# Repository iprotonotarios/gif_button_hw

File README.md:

# gif_button_hw
KiCad design files for gif_button

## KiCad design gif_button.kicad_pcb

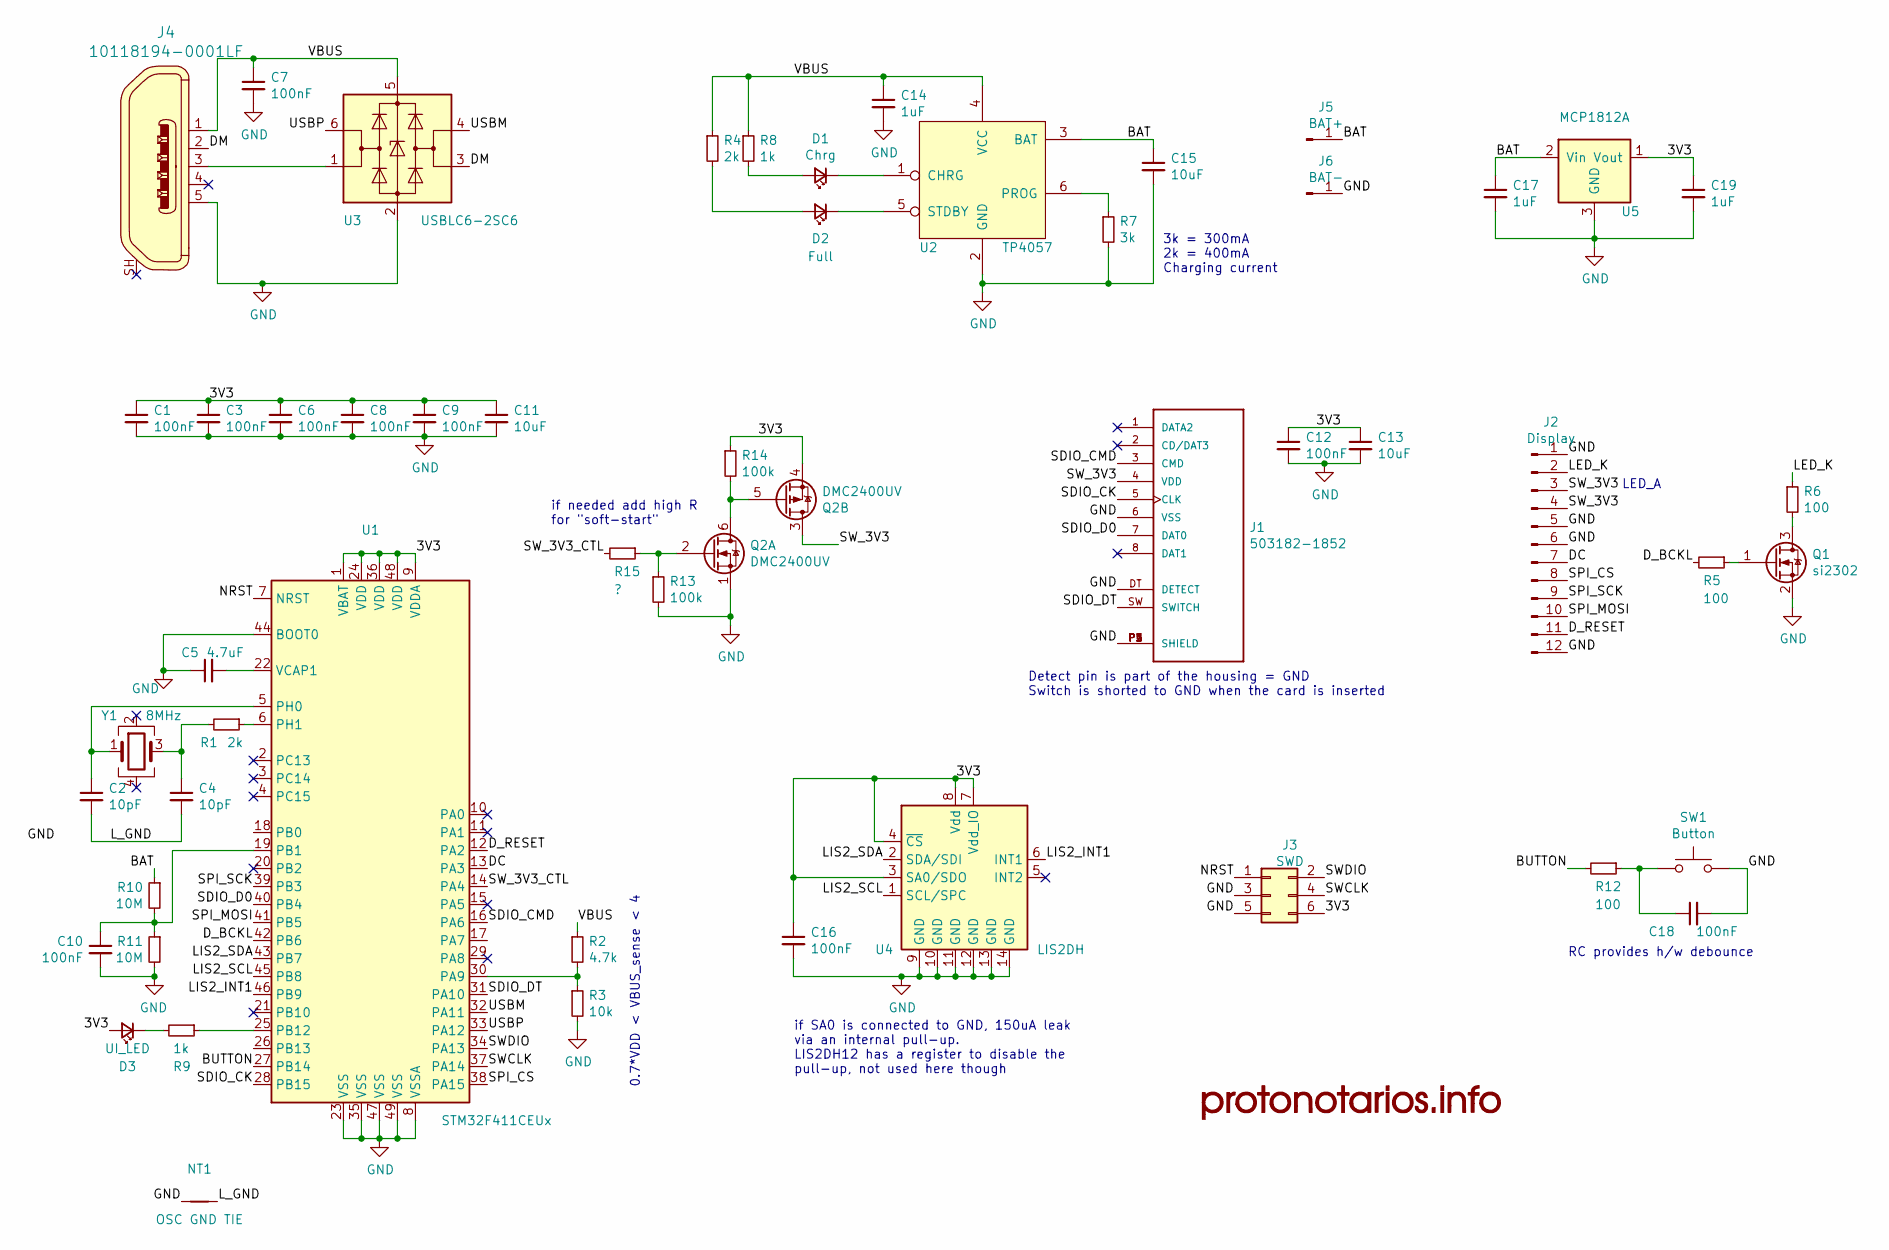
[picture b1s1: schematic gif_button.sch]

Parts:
C1, C3, C6, C7, C8, C9, C10, C12, C16, C18: 100nF; C_0603_1608Metric
C2, C4: 10pF; C_0402_1005Metric
C5: 4.7uF; C_0603_1608Metric
C11, C13, C15: 10uF; C_0805_2012Metric
C14, C17, C19: 1uF; C_0603_1608Metric
D1: Chrg; LED_0603_1608Metric
D2: Full; LED_0603_1608Metric
D3: UI_LED; LED_0603_1608Metric
G1: protonotarios.info; logo_small
J1: 503182-1852; MOLEX_503182-1852
J2: Display; IPS_240_240
J3: SWD; PinHeader_2x03_P1.27mm_Vertical
J4: 10118194-0001LF; USB_Micro_B_Female_10118194-0001LF; MPN 10118194-0001LF; Digi-Key_PN 609-4618-1-ND
J5: BAT+; SolderWire-0.75sqmm_1x01_D1.25mm_OD2.3mm
J6: BAT-; SolderWire-0.75sqmm_1x01_D1.25mm_OD2.3mm
NT1: OSC GND TIE; NetTie-2_SMD_Pad0.5mm
Q1: si2302; SOT-23
Q2: DMC2400UV; SOT-563
R1: 2k; R_0402_1005Metric
R2: 4.7k; R_0603_1608Metric
R3: 10k; R_0603_1608Metric
R4: 2k; R_0603_1608Metric
R5, R6, R12: 100; R_0603_1608Metric
R7: 3k; R_0603_1608Metric
R8, R9: 1k; R_0603_1608Metric
R10, R11: 10M; R_0603_1608Metric
R13, R14: 100k; R_0603_1608Metric
R15: ?; R_0603_1608Metric
SW1: Button; SW_SPST_PTS810
U1: STM32F411CEUx; QFN-48-1EP_7x7mm_P0.5mm_EP5.6x5.6mm
U2: TP4057; SOT-23-6
U3: USBLC6-2SC6; SOT-23-6
U4: LIS2DH; LGA-14_2x2mm_P0.35mm_LayoutBorder3x4y
U5: MCP1812A; SOT-23
Y1: 8MHz; Crystal_SMD_3225-4Pin_3.2x2.5mm

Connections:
/3V3: C1.1, C3.1, C6.1, C8.1, C9.1, C11.1, C12.1, C13.1, C16.1, C19.1, D3.2 (A), J3.6, Q2.4 (S), R14.1, U1.1 (VBAT), U1.9 (VDDA), U1.24 (VDD), U1.36 (VDD), U1.48 (VDD), U4.3 (SA0/SDO), U4.4 (~CS), U4.7 (Vdd_IO), U4.8 (Vdd), U5.1 (Vout)
/BAT: C15.1, C17.1, J5.1, R10.1, U2.3 (BAT), U5.2 (Vin)
/BUTTON: R12.2, U1.27 (PB14)
/DC: J2.7, U1.13 (PA3)
/DM: J4.2, U3.3 (I/O2)
/D_BCKL: R5.2, U1.42 (PB6)
/D_RESET: J2.11, U1.12 (PA2)
/LED_K: J2.2, R6.1
/LIS2_INT1: U1.46 (PB9), U4.6 (INT1)
/LIS2_SCL: U1.45 (PB8), U4.1 (SCL/SPC)
/LIS2_SDA: U1.43 (PB7), U4.2 (SDA/SDI)
/L_GND: C2.2, C4.2, NT1.2
/NRST: J3.1, U1.7 (NRST)
/SDIO_CK: J1.5 (CLK), U1.28 (PB15)
/SDIO_CMD: J1.3 (CMD), U1.16 (PA6)
/SDIO_D0: J1.7 (DAT0), U1.40 (PB4)
/SDIO_DT: J1.SW (SWITCH), U1.31 (PA10)
/SPI_CS: J2.8, U1.38 (PA15)
/SPI_MOSI: J2.10, U1.41 (PB5)
/SPI_SCK: J2.9, U1.39 (PB3)
/SWCLK: J3.4, U1.37 (PA14)
/SWDIO: J3.2, U1.34 (PA13)
/SW_3V3: J1.4 (VDD), J2.3, J2.4, Q2.3 (D)
/SW_3V3_CTL: R15.2, U1.14 (PA4)
/USBM: U1.32 (PA11), U3.4 (I/O2)
/USBP: U1.33 (PA12), U3.6 (I/O1)
/VBUS: C7.1, C14.1, J4.1, R2.1, R4.1, R8.1, U2.4 (VCC), U3.5 (VBUS)
GND: C1.2, C3.2, C5.1, C6.2, C7.2, C8.2, C9.2, C10.2, C11.2, C12.2, C13.2, C14.2, C15.2, C16.2, C17.2, C18.2, C19.2, J1.6 (VSS), J1.DT (DETECT), J1.P1 (SHIELD), J1.P2 (SHIELD), J1.P3 (SHIELD), J1.P4 (SHIELD), J1.P5 (SHIELD), J2.1, J2.5, J2.6, J2.12, J3.3, J3.5, J4.5, J6.1, NT1.1, Q1.2 (S), Q2.1 (S), R3.2, R7.2, R11.2, R13.2, SW1.2, U1.8 (VSSA), U1.23 (VSS), U1.35 (VSS), U1.44 (BOOT0), U1.47 (VSS), U1.49 (VSS), U2.2 (GND), U3.2 (GND), U4.9 (GND), U4.10 (GND), U4.11 (GND), U4.12 (GND), U4.13 (GND), U4.14 (GND), U5.3 (GND)
unnamed: C2.1, U1.5 (PH0), Y1.1
unnamed: C4.1, R1.2, Y1.3
unnamed: C5.2, U1.22 (VCAP1)
unnamed: C10.1, R10.2, R11.1, U1.19 (PB1)
unnamed: C18.1, R12.1, SW1.1
unnamed: D1.1 (K), U2.1 (CHRG)
unnamed: D1.2 (A), R8.2
unnamed: D2.1 (K), U2.5 (STDBY)
unnamed: D2.2 (A), R4.2
unnamed: D3.1 (K), R9.2
unnamed: J4.3, U3.1 (I/O1)
unnamed: Q1.1 (G), R5.1
unnamed: Q1.3 (D), R6.2
unnamed: Q2.2 (G), R13.1, R15.1
unnamed: Q2.5 (G), Q2.6 (D), R14.2
unnamed: R1.1, U1.6 (PH1)
unnamed: R2.2, R3.1, U1.30 (PA9)
unnamed: R7.1, U2.6 (PROG)
unnamed: R9.1, U1.25 (PB12)

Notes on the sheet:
LED_A
3k = 300mA 2k = 400mA Charging current
RC provides h/w debounce
if SA0 is connected to GND, 150uA leak via an internal pull-up. LIS2DH12 has a register to disable the pull-up, not used here though
if needed add high R for "soft-start"
0.7*VDD < VBUS_sense < 4
Detect pin is part of the housing = GND Switch is shorted to GND when the card is inserted

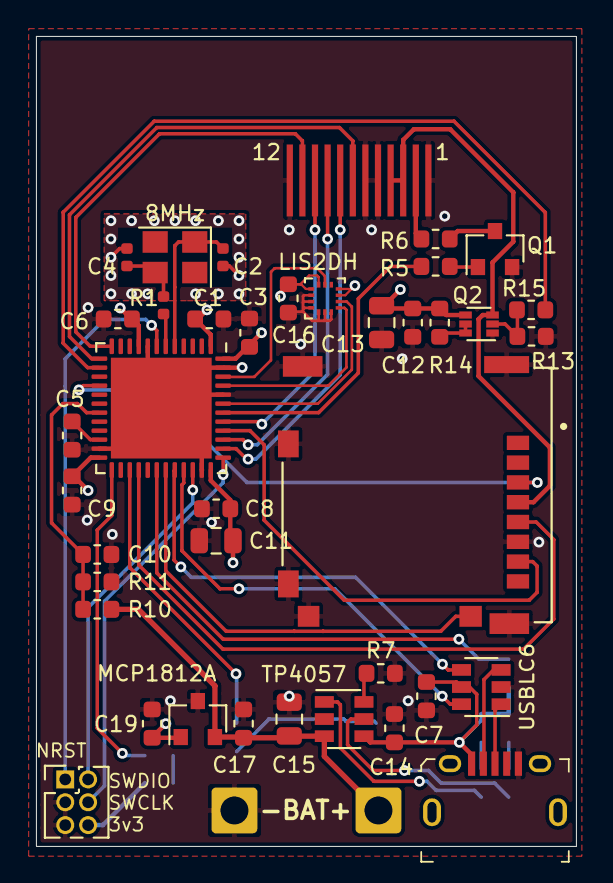
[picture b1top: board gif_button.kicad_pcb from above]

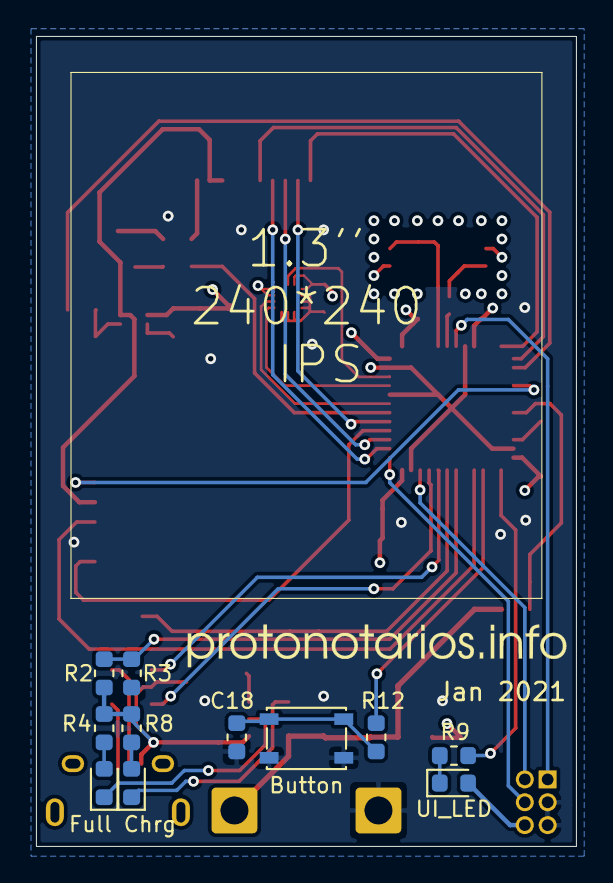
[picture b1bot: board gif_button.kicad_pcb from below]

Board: 4 copper layers, 30.0 x 45.0 mm, 54 parts (12 on the bottom side), 47 nets.

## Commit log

2021-02-09 first public commit
